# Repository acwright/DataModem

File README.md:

DataModem
=========

Data (RS-232/Serial) to Audio Modem

Usage
-----

Connect the DataModem to your computer's serial port (or USB-to-Serial adapter) and to an audio input/output device (like a cassette recorder or audio interface). Use terminal software to send and receive data through the modem.

Configuration
--------------

- **Baud Rate**: 300 baud (recommended for best reliability)
- **Tone Frequency**: Approximately 4kHz
- **RV1**: Adjusts output signal strength to the cassette recorder
- **RV2**: Adjusts the triggering sensitivity of the Schmitt trigger for playback

How It Works
------------

The DataModem uses a simple one-tone encoding system where the presence of a tone represents a 1 bit and silence represents a 0 bit.

**Recording Data**: When transmitting, a 555 timer (U2) generates a ~4kHz square wave tone when the UART input is high. The tone is buffered and AC-coupled before being fed to the cassette recorder input. When the UART input is low, the 555 is disabled and produces no tone.

**Playing Back Data**: During playback, a Schmitt trigger detects the presence of the recorded tone. A retriggerable 555 monostable circuit (U3) converts the rapid tone pulses into a steady output signal. The monostable stays on for 300μs when triggered, and continuous triggers from the 4kHz tone keep it active, producing a clean digital output that matches the original UART signal.

The circuit is designed for 300 baud operation, providing excellent reliability with minimal bit loss when properly calibrated.

Licence
-------

This project is licensed under the CERN Open Hardware Licence Version 2 - Permissive License - see the [LICENSE](LICENSE) file for details.

Credits
-------

This project is inspired by and based on the following works:

- [Datacorder](https://www.mitchelectronics.co.uk/documents/DATACORD.pdf) by Mitchell Electronics
- [UART Cassette Tape Interface](https://maker.pro/pcb/projects/make-uart-cassette-tape-interface) by Robin Mitchell

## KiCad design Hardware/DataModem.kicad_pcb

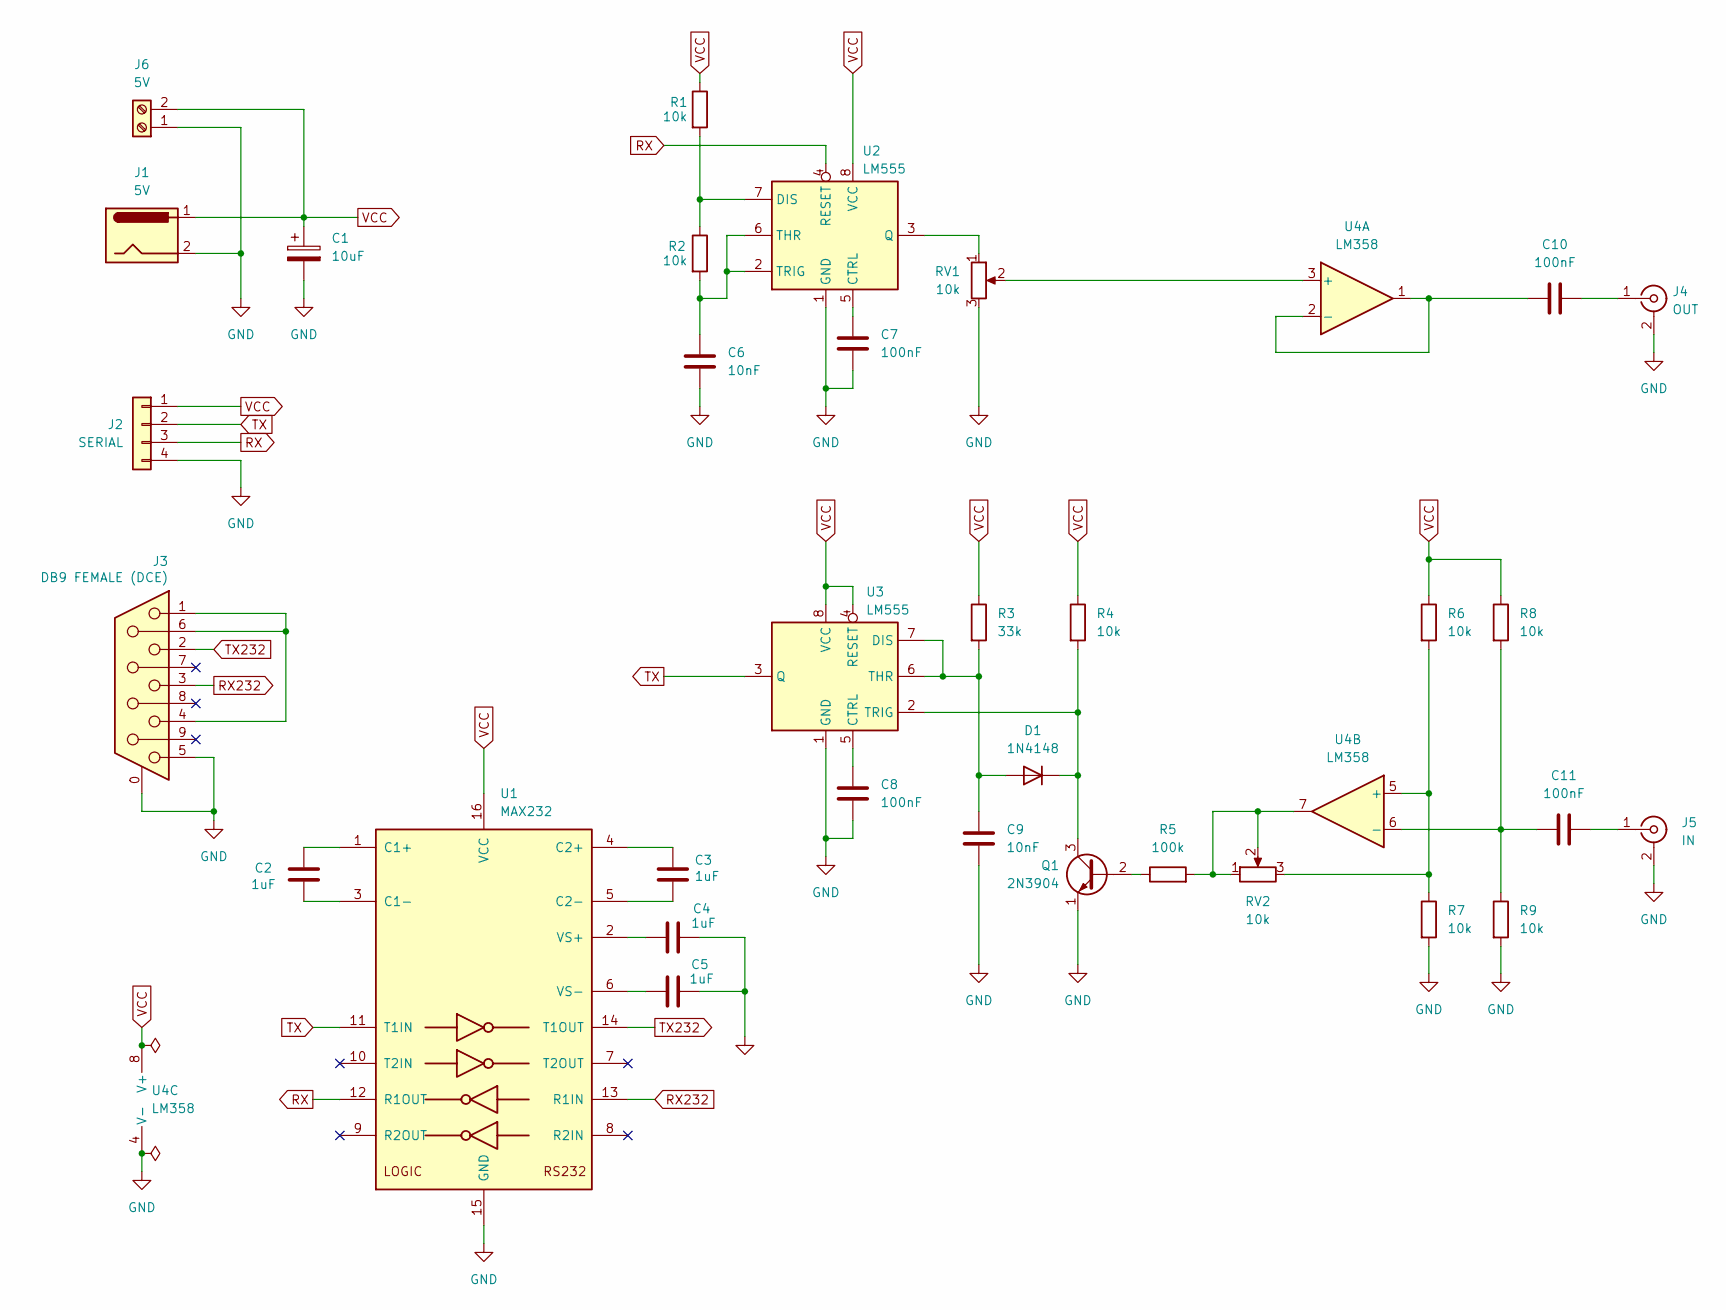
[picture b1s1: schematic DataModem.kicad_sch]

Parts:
C1: 10uF; CP_Radial_D5.0mm_P2.50mm
C2, C3, C4, C5: 1uF; C_Disc_D5.0mm_W2.5mm_P2.50mm; LCSC C28323
C6, C9: 10nF; C_Disc_D5.0mm_W2.5mm_P2.50mm
C7, C8, C10, C11: 100nF; C_Disc_D5.0mm_W2.5mm_P2.50mm
D1: 1N4148; D_DO-35_SOD27_P7.62mm_Horizontal
J1: 5V; BarrelJack_CUI_PJ-063AH_Horizontal
J2: SERIAL; PinHeader_1x04_P2.54mm_Horizontal
J3: DB9 FEMALE (DCE); DSUB-9_Socket_Horizontal_P2.77x2.84mm_EdgePinOffset7.70mm_H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; MPN D09S33E4GX00LF; Digikey 609-1487-ND
J4: OUT; SWITCHCRAFT_PJRAN1X1U02X
J5: IN; SWITCHCRAFT_PJRAN1X1U02X
J6: 5V; TerminalBlock_Phoenix_MKDS-1,5-2-5.08_1x02_P5.08mm_Horizont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
Q1: 2N3904; TO-92_Inline
R1, R2, R4, R6, R7, R8, R9: 10k; R_Axial_DIN0204_L3.6mm_D1.6mm_P5.08mm_Horizontal
R3: 33k; R_Axial_DIN0204_L3.6mm_D1.6mm_P5.08mm_Horizontal
R5: 100k; R_Axial_DIN0204_L3.6mm_D1.6mm_P5.08mm_Horizontal
RV1, RV2: 10k; 3386F-1-103LF
U1: MAX232; DIP-16_W7.62mm_Socket_LongPads; LCSC C59824
U2, U3: LM555; DIP-8_W7.62mm
U4: LM358; DIP-8_W7.62mm

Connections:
GND: C1.2, C4.2, C5.2, C6.2, C7.2, C8.2, C9.1, J1.2, J2.4, J3.0 (PAD), J3.5, J4.2 (Ext), J5.2 (Ext), J6.1, Q1.1 (E), R7.2, R9.2, RV1.3, U1.15 (GND), U2.1 (GND), U3.1 (GND), U4.4 (V-)
unnamed: C9.2, D1.2 (A), R3.2, U3.6 (THR), U3.7 (DIS)
unnamed: D1.1 (K), Q1.3 (C), R4.2, U3.2 (TRIG)
unnamed: J3.1, J3.4, J3.6
unnamed: C10.2, J4.1 (In)
unnamed: C11.1, J5.1 (In)
unnamed: Q1.2 (B), R5.1
unnamed: R5.2, RV2.1, RV2.2, U4.7
unnamed: C2.1, U1.1 (C1+)
unnamed: C2.2, U1.3 (C1-)
unnamed: C3.1, U1.4 (C2+)
unnamed: C3.2, U1.5 (C2-)
unnamed: C4.1, U1.2 (VS+)
unnamed: C5.1, U1.6 (VS-)
unnamed: C7.1, U2.5 (CTRL)
unnamed: R1.2, R2.1, U2.7 (DIS)
unnamed: RV1.1, U2.3 (Q)
unnamed: C6.1, R2.2, U2.2 (TRIG), U2.6 (THR)
unnamed: C8.1, U3.5 (CTRL)
unnamed: RV1.2, U4.3 (+)
unnamed: C10.1, U4.1, U4.2 (-)
unnamed: R6.2, R7.1, RV2.3, U4.5 (+)
unnamed: C11.2, R8.2, R9.1, U4.6 (-)
RX: J2.3, U1.12 (R1OUT), U2.4 (RESET)
RX232: J3.3, U1.13 (R1IN)
TX: J2.2, U1.11 (T1IN), U3.3 (Q)
TX232: J3.2, U1.14 (T1OUT)
VCC: C1.1, J1.1, J2.1, J6.2, R1.1, R3.1, R4.1, R6.1, R8.1, U1.16 (VCC), U2.8 (VCC), U3.4 (RESET), U3.8 (VCC), U4.8 (V+)

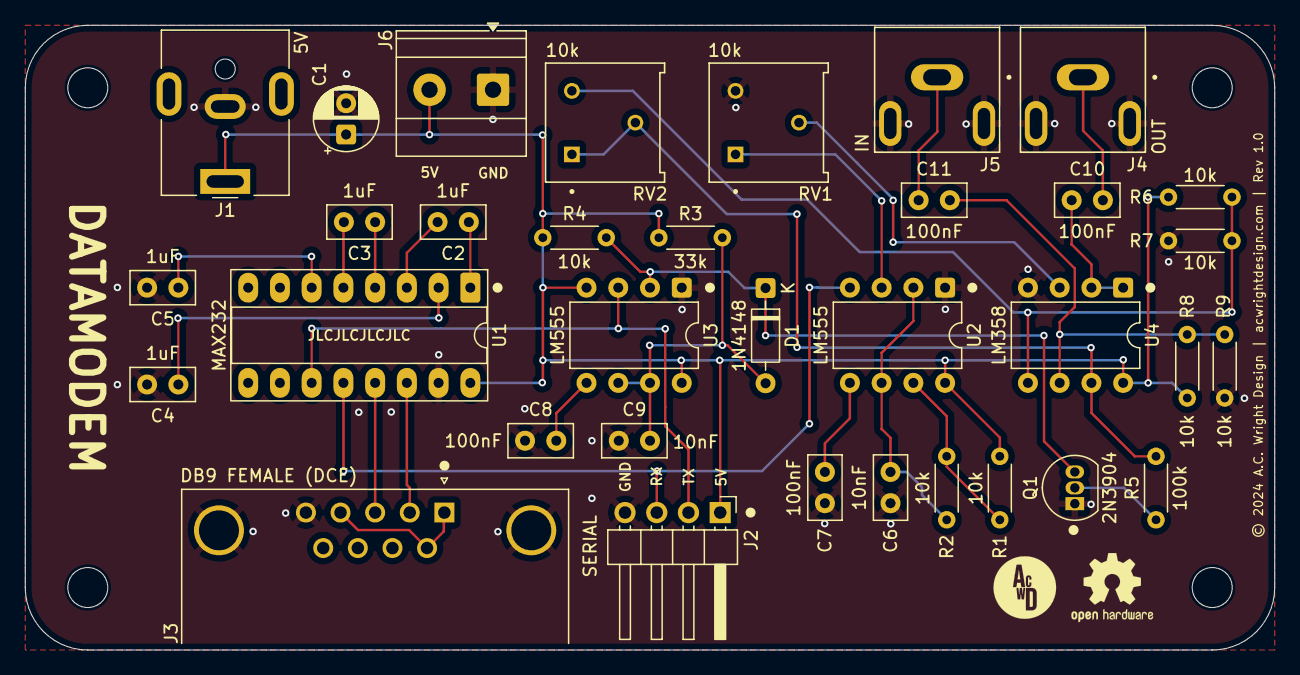
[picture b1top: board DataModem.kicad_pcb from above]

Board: 2 copper layers, 100.0 x 50.0 mm, 34 parts (0 on the bottom side), 28 nets.

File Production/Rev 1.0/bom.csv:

Designator,Footprint,Quantity,Value,LCSC Part #
C1,CP_Radial_D5.0mm_P2.50mm,1,10uF,
"C10, C11, C7, C8",C_Disc_D5.0mm_W2.5mm_P2.50mm,4,100nF,
"C2, C3, C4, C5",C_Disc_D5.0mm_W2.5mm_P2.50mm,4,1uF,C28323
"C6, C9",C_Disc_D5.0mm_W2.5mm_P2.50mm,2,10nF,
D1,D_DO-35_SOD27_P7.62mm_Horizontal,1,1N4148,
J1,BarrelJack_CUI_PJ-063AH_Horizontal,1,5V,
J2,PinHeader_1x04_P2.54mm_Horizontal,1,SERIAL,
J4,SWITCHCRAFT_PJRAN1X1U02X,1,OUT,
J5,SWITCHCRAFT_PJRAN1X1U02X,1,IN,
J6,"TerminalBlock_Phoenix_MKDS-1,5-2-5.08_1x02_P5.08mm_Horizontal",1,5V,
Q1,TO-92_Inline,1,2N3904,
"R1, R2, R4, R6, R7, R8, R9",R_Axial_DIN0204_L3.6mm_D1.6mm_P5.08mm_Horizontal,7,10k,
R3,R_Axial_DIN0204_L3.6mm_D1.6mm_P5.08mm_Horizontal,1,33k,
R5,R_Axial_DIN0204_L3.6mm_D1.6mm_P5.08mm_Horizontal,1,100k,
"RV1, RV2",3386F-1-103LF,2,10k,
U1,DIP-16_W7.62mm_Socket_LongPads,1,MAX232,C59824
"U2, U3",DIP-8_W7.62mm,2,LM555,
U4,DIP-8_W7.62mm,1,LM358,

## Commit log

2026-01-04 Enhance README with project description
    Added a description for the DataModem project.
2026-01-04 Add PCB
2026-01-04 Add screw terminal for power input
2026-01-04 Add image to README
2026-01-15 Production fixes

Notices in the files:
Hardware/DataModem.kicad_pcb:
© 2024 A.C. Wright Design | acwrightdesign.com | Rev 1.0
